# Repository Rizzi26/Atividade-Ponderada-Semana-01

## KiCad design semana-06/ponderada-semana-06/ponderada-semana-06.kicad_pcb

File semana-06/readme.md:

# Atividade ponderada semana 06
## Qual o objetivo da atividade?

&emsp;A atividade tem como objetivo desenvolver um esquemático e uma PCB para familiarizar o aluno com o software kicad e estimular seu aprendizado de uma nova ferramenta.

## Arquivos abrigados:

&emsp;O arquivo "ponderada-semana-06.kicad_sch" abriga o esquematico do meu cricuito. Ele apresenta o desenho da placa com o circuito, suas respectivas ligações e saidas entre os compontentes ali presentes.

&emsp;O arquivo "ponderada-semana-06_pcb" abriga o a visualização da impressão final da minha placa, mostrando inclusive em 3D como irá ficar o seu processo de montagem final.

## O repositorio esta organizado da seguinte maneira:

```
Atividades-ponderadas-M5/
|
|--flask-test/
|--semana-01/
|--semana-03/
|--semana-06/
|  |--ponderada-semana-06/
|  |  |--ponderada-semana-06.kicad_sch
|  |  |--ponderada-semana-06.kicad_pcb
|  |--readme.md         
|--semana-07/
```

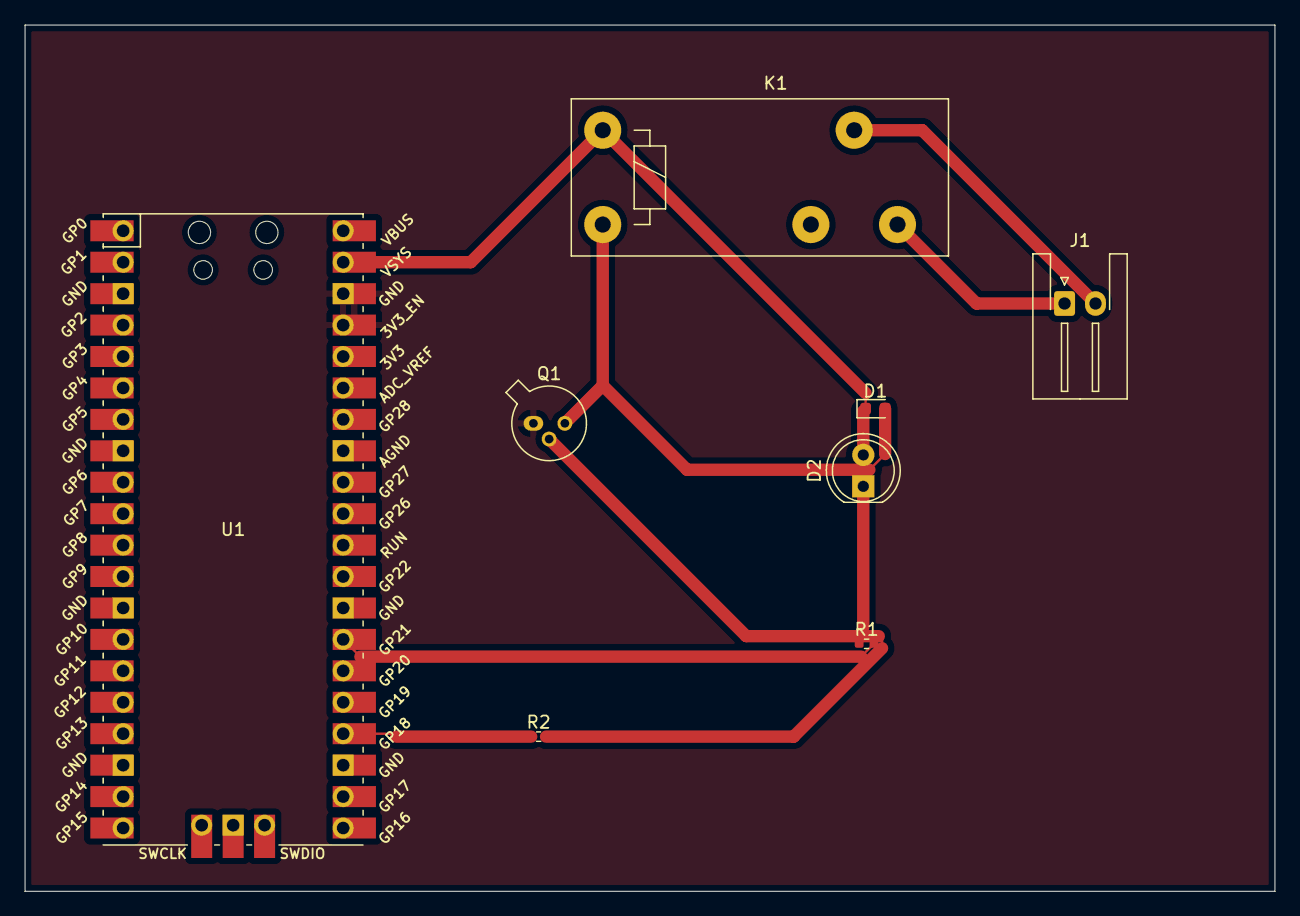
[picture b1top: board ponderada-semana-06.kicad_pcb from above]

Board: 2 copper layers, 101.0 x 70.0 mm, 8 parts (0 on the bottom side), 5 nets.

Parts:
D1: D; D_0603_1608Metric
D2: LED; LED_D5.0mm_Clear
J1: Conn_01x02_Socket; JST_XH_S2B-XH-A-1_1x02_P2.50mm_Horizontal
K1: Relay_SPDT; Relay_SPDT_Schrack-RT1-FormC_RM3.5mm
Q1: BC107; TO-18-3
R1, R2: R; R_0402_1005Metric_Pad0.72x0.64mm_HandSolder
U1: Pico; RPi_Pico_SMD_TH

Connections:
GND: Q1.1 (E), U1.37 (3V3_EN), U1.38 (GND)
unnamed: J1.1, K1.14
unnamed: J1.2, K1.11
unnamed: D1.1 (K), D1.2 (A), D2.1 (K), D2.2 (A), K1.A1, K1.A2, Q1.2 (B), Q1.3 (C), R1.1, R1.2, R2.2, U1.26 (GPIO20), U1.27 (GPIO21), U1.39 (VSYS)
Sinal: R2.1, U1.24 (GPIO18)

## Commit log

2024-02-08 criando meu primeirp projeto docusauros
2024-02-08 apagando o arquivo readme.md
2024-02-08 iniciando a construção da minha pagina pessoal
2024-02-08 ajustes em minha pagina pessoal
2024-02-09 deploy
2024-02-09 fixed deploy
2024-02-09 Fixed my curriculum and estructure
2024-02-19 alterando caminho da atvd semana 01
2024-02-19 update caminho
2024-02-19 update name path
2024-02-19 add dependecies
2024-02-19 mudando o nome da pasta de semanas
2024-02-28 atividade ponderada semana 03
2024-03-23 projeto inicial
2024-03-29 Atividade-ponderada-semana-06
    Atividade ponderada semana 06 e inicio da atividade semana 07
2024-04-04 update ponderada
2024-04-04 atividade ponderada 1.0v
